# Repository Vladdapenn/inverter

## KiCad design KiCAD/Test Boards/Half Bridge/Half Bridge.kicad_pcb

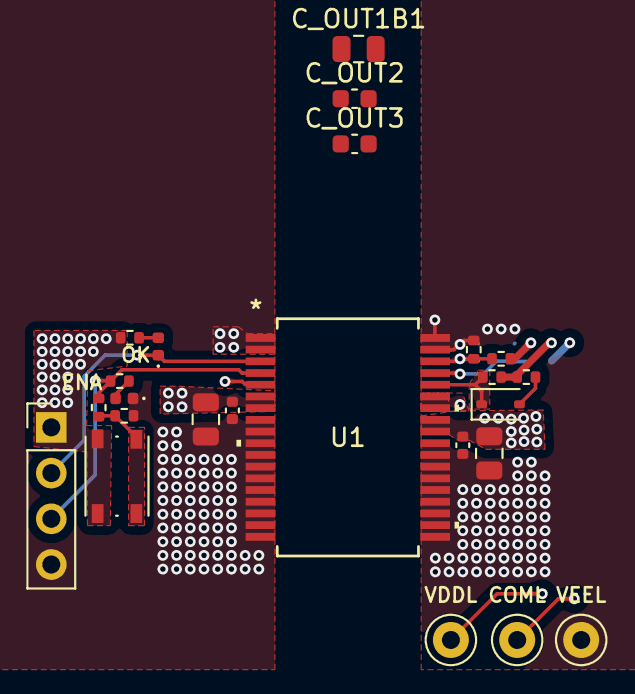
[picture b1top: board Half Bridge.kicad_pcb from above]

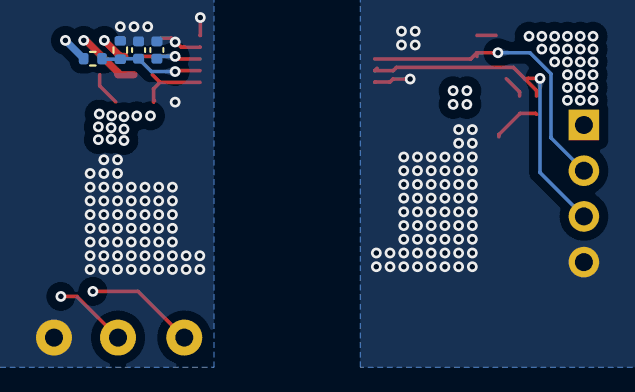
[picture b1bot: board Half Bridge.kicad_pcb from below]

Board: 4 copper layers, 28 parts (4 on the bottom side), 14 nets.

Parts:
C1, C4: .1u; C_0402_1005Metric
C2: 20u; C_0805_2012Metric
C5: 10u; C_0805_2012Metric
COML: TestPoint; TestPoint_Keystone_5000-5004_Miniature
C_FBVDD1: 330p; C_0402_1005Metric
C_FBVEE1: 330p; C_0402_1005Metric
C_OUT1B1: 10u±10%; C_0805_2012Metric
C_OUT2: 1u±10%; C_0603_1608Metric
C_OUT3: 3.3u±10%; C_0603_1608Metric
D1, D2: LED; LED_0402_1005Metric
D_LIM1: RB500V-40H RRG; D_SOD-323
J1: Conn_01x04_Pin; PinHeader_1x04_P2.54mm_Vertical
R1, R2: 10k; R_0402_1005Metric
R3: 7k; R_0402_1005Metric
R4: 3k; R_0402_1005Metric
R_FBVDD_BOT1: 12k; R_0402_1005Metric
R_FBVDD_TOP1: 100k; R_0402_1005Metric
R_FBVEE_BOT1: 100k; R_0402_1005Metric
R_FBVEE_TOP1: 100k; R_0402_1005Metric
R_LIM1: 10k; R_0402_1005Metric
R_LIM2: 250; R_0402_1005Metric
SW1: SW_Push; SW_Push_1P1T_NO_Vertical_Wuerth_434133025816
U1: PUCC14141QDWNQ1; SSOP36
VDDL: TestPoint; TestPoint_Keystone_5000-5004_Miniature
VEEL: TestPoint; TestPoint_Keystone_5000-5004_Miniature

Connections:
/*PGL: D1.1 (K), J1.2, U1.3 (*PG)
/ENAL: J1.3, R3.2, R4.1, U1.4 (ENA)
/GNDP: C1.2, C2.2, D2.1 (K), J1.4, R2.2, U1.1 (GNDP), U1.2 (GNDP), U1.5 (GNDP), U1.8 (GNDP), U1.9 (GNDP), U1.10 (GNDP), U1.11 (GNDP), U1.12 (GNDP), U1.13 (GNDP), U1.14 (GNDP), U1.15 (GNDP), U1.16 (GNDP), U1.17 (GNDP), U1.18 (GNDP)
/UCC14141/COM: COML.1, C_OUT2.2, C_OUT3.1, R_FBVEE_TOP1.1, R_LIM1.2, R_LIM2.2
/UCC14141/FBVDD: C_FBVDD1.1, R_FBVDD_BOT1.1, R_FBVDD_TOP1.2, U1.34 (FBVDD)
/UCC14141/FBVEE: C_FBVEE1.1, R_FBVEE_BOT1.1, R_FBVEE_TOP1.2, U1.33 (FBVEE)
/UCC14141/RLIM: D_LIM1.1 (K), R_LIM1.1, U1.32 (RLIM)
/UCC14141/VDD: C4.1, C5.1, C_OUT1B1.1, C_OUT2.1, R_FBVDD_TOP1.1, U1.28 (VDD), U1.29 (VDD), VDDL.1
/UCC14141/VEE: C4.2, C5.2, C_FBVDD1.2, C_FBVEE1.2, C_OUT1B1.2, C_OUT3.2, R_FBVDD_BOT1.2, R_FBVEE_BOT1.2, U1.19 (VEE), U1.20 (VEE), U1.21 (VEE), U1.22 (VEE), U1.23 (VEE), U1.24 (VEE), U1.25 (VEE), U1.26 (VEE), U1.27 (VEE), U1.30 (VEE), U1.31 (VEE), U1.35 (VEEA), U1.36 (VEE), VEEL.1
/VIN: C1.1, C2.1, J1.1, R1.1, SW1.1, U1.6 (VIN), U1.7 (VIN)
unnamed: D1.2 (A), R1.2
unnamed: D2.2 (A), R4.2
unnamed: D_LIM1.2 (A), R_LIM2.1
unnamed: R2.1, R3.1, SW1.2
